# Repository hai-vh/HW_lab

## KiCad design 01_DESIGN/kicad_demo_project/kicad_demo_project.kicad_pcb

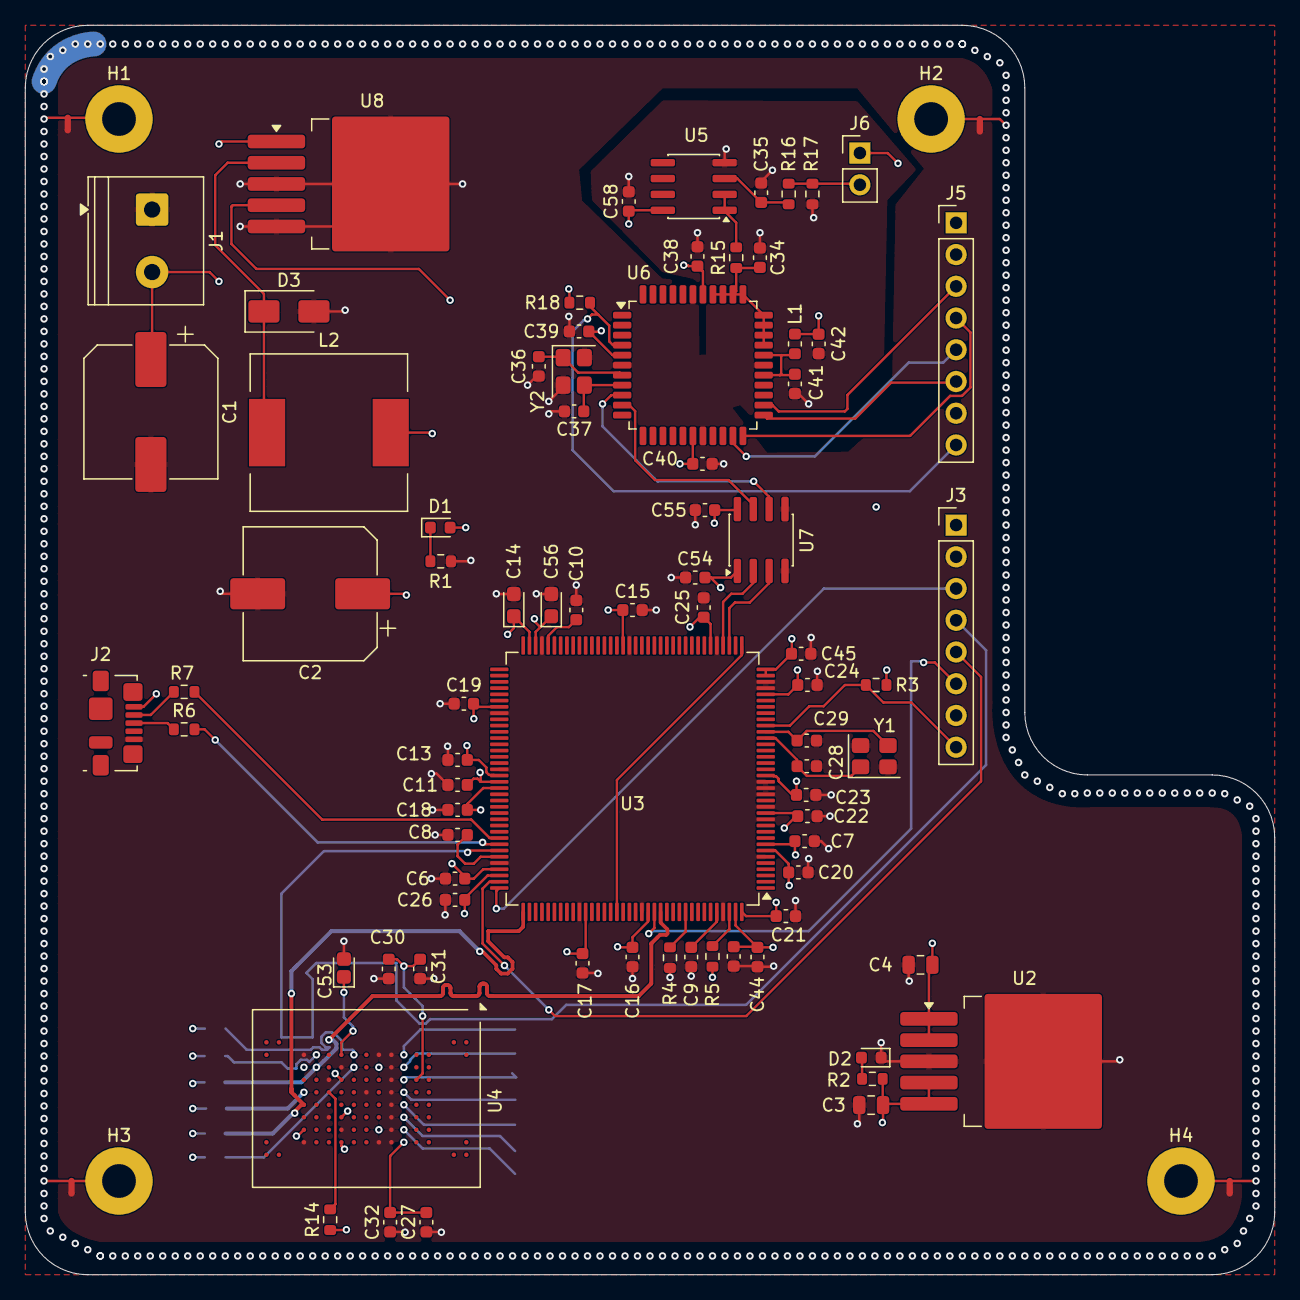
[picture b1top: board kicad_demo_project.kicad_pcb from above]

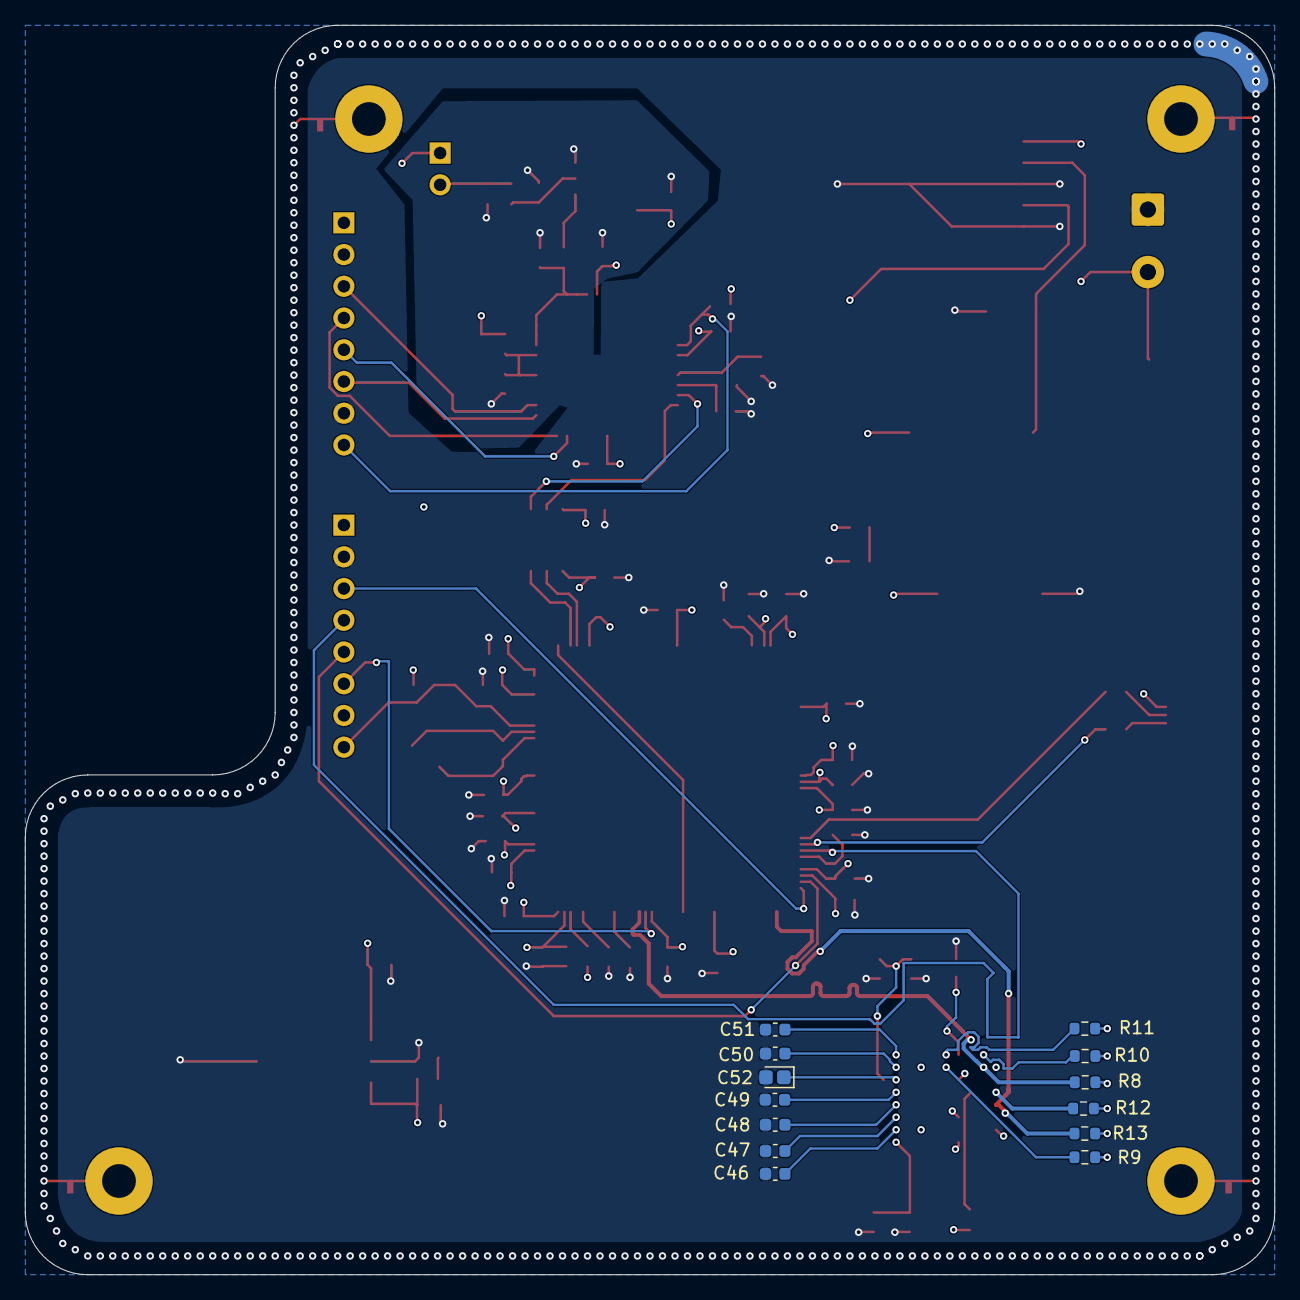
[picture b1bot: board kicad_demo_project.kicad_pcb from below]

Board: 4 copper layers, 100.0 x 100.0 mm, 99 parts (13 on the bottom side), 49 nets.

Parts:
C1: 680uF; CP_Elec_10x10.5
C2: 220uF; CP_Elec_10x10.5
C3, C4: 10uF; C_0805_2012Metric
C6, C7, C11, C15, C16, C17, C18, C19, C20, C21, C22, C23, C24, C25, C26, C27, C30, C32, C34, C35, C38, C39, C40, C41, C42, C44, C45, C46, C47, C48, C49, C50, C51, C54, C55, C58: 0.1uF/6.3V; C_0603_1608Metric
C8, C9, C10, C13: 4.7uF/6.3V; C_0603_1608Metric
C14, C56: 4.7uF; CP_EIA-2012-15_AVX-P
C28, C29, C36, C37: 16pF/6.3V; C_0603_1608Metric
C31: 1uF/6.3V; C_0603_1608Metric
C43: 0.1uF/6.3V; CAP_C_1608X80
C52, C53: 4.7uF; CP_EIA-1608-10_AVX-L
D1, D2: 150060YS75000; LED_0603_1608Metric
D3: SS34; D_SMA
H1, H2, H3, H4: MountingHole_Pad; MountingHole_2.7mm_M2.5_Pad
J1: Screw_Terminal_01x02; TerminalBlock_Phoenix_PT-1,5-2-5.0-H_1x02_P5.00mm_Horizontal
J2: 0473460001; USB_Micro-B_Molex_47346-0001
J3, J5: Conn_01x08; PinHeader_1x08_P2.54mm_Vertical
J6: Conn_01x02; PinHeader_1x02_P2.54mm_Vertical
L1: 10uH/250mA; L_0603_1608Metric
L2: 47uH; L_12x12mm_H8mm
NT1, NT2, NT3, NT4: NetTie_2; NetTie-2_SMD_Pad0.5mm
R1, R2: 1k; R_0603_1608Metric
R3, R4, R5, R14, R18: 4.7k; R_0603_1608Metric
R6, R7: 0R/DNP; R_0603_1608Metric
R8, R9, R10, R11, R12, R13, R17: 10k; R_0603_1608Metric
R15, R16: 22R; R_0603_1608Metric
U2: TPS7A4533DCQR; TO-263-5_TabPin3
U3: STM32H745ZIT3; LQFP-144_20x20mm_P0.5mm
U4: MTFC32GAZAQDW-AAT; BGA-100_14x18mm_Layout10x17_P1mm
U5: OPA2340; SOIC-8_3.9x4.9mm_P1.27mm
U6: ATMEGA324PA; TQFP-44_10x10mm_P0.8mm
U7: ISO7721DR; SOIC-8_3.9x4.9mm_P1.27mm
U8: LM2596S-5; TO-263-5_TabPin3
Y1, Y2: Crystal_GND24; Crystal_SMD_3225-4Pin_3.2x2.5mm

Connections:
+3.3V: C3.1, C6.2, C7.2, C11.2, C13.2, C14.1, C15.2, C16.2, C17.2, C18.2, C19.2, C20.2, C21.2, C22.2, C23.2, C24.2, C25.2, C26.2, C27.2, C32.2, C43.2, C44.2, C45.2, C46.2, C47.2, C48.2, C49.2, C50.2, C51.2, C52.1, C53.1, C54.2, C56.1, J3.1, R2.2, R3.1, R5.1, R8.2, R9.2, R10.2, R11.2, R12.2, R13.2, R14.1, U2.4 (OUT), U2.5 (SENSE), U3.7 (VDD), U3.8 (VBAT), U3.13 (VDD), U3.19 (VDD), U3.32 (VDD), U3.35 (VREF+), U3.36 (VDDA), U3.42 (VDD), U3.56 (VDD), U3.70 (VDDLDO), U3.71 (VDD), U3.79 (VDD), U3.90 (VDD50USB), U3.91 (VDD33USB), U3.92 (VDD), U3.105 (VDDLDO), U3.106 (VDD), U3.119 (VDD), U3.129 (VDD), U3.143 (VDDLDO), U3.144 (VDD), U4.F2 (VCC), U4.F3 (VCC), U4.F4 (VCC), U4.F5 (VCC), U4.F6 (VCC), U4.F7 (VCC), U4.F8 (VCC), U4.F9 (VCC), U4.H3 (VCCQ), U4.H8 (VCCQ), U4.L2 (VCCQ), U4.L4 (VCCQ), U4.L7 (VCCQ), U4.L9 (VCCQ), U4.P3 (VCCQ), U4.P8 (VCCQ), U7.1 (VCC1)
+5V: C2.1, C4.1, C38.2, C39.2, C40.2, C42.2, C55.2, C58.1, D1.2 (A), J2.1 (VBUS), J5.1, J6.1, L1.2, L2.2, R18.2, U2.1 (~SHDN), U2.2 (IN), U5.8 (V+), U6.5 (VCC), U6.17 (VCC), U6.38 (VCC), U7.8 (VCC2), U8.4 (FB)
+5V_AVCC: C41.2, L1.1, U6.27 (AVCC), U6.29 (AREF)
+12V: C1.1, J1.2, U8.1 (VIN)
/AVR/ADC_TEMP1: C34.2, R15.1, U6.30 (PA7_(ADC7/PCINT7)), U6.31 (PA6_(ADC6/PCINT6)), U6.32 (PA5_(ADC5/PCINT5)), U6.33 (PA4_(ADC4/PCINT4)), U6.34 (PA3_(ADC3/PCINT3)), U6.35 (PA2_(ADC2/PCINT2)), U6.36 (PA1_(ADC1/PCINT1)), U6.37 (PA0_(ADC0/PCINT0))
/AVR/AVR_JTAG_TCK: J5.5, U6.21 (PC2_(PCINT18/TCK))
/AVR/AVR_JTAG_TDI: J5.3, U6.24 (PC5_(TDI/PCINT21))
/AVR/AVR_JTAG_TDO: J5.6, U6.23 (PC4_(TDO/PCINT20))
/AVR/AVR_JTAG_TMS: J5.4, U6.22 (PC3_(PCINT19/TMS))
/AVR/AVR_JTAG_nRESET: J5.8, R18.1, U6.4 (~RESET)
/AVR/NTC1-: J6.2, R16.2, R17.1
/MCU/MCU_BOOT0: R4.2, U3.135 (BOOT0)
/MCU/MCU_JTAG_TCK: J3.5, U3.107 (PA14)
/MCU/MCU_JTAG_TDI: J3.3, U3.108 (PA15)
/MCU/MCU_JTAG_TDO: J3.6, U3.130 (PB3)
/MCU/MCU_JTAG_TMS: J3.4, U3.102 (PA13)
/MCU/MCU_JTAG_nRESET: J3.8, R3.2, U3.27 (~RST)
/MCU/MCU_OSCIN: C28.1, U3.25 (PH0-OSC_IN), Y1.1
/MCU/MCU_OSCOUT: C29.1, U3.26 (PH1-OSC_OUT), Y1.3
/MCU/MCU_PDR: R5.2, U3.142 (PDR_ON)
/MCU/MCU_VCAP1: C10.2, U3.68 (VCAP)
/MCU/MCU_VCAP2: C8.2, U3.103 (VCAP)
/MCU/MCU_VCAP3: C9.2, U3.140 (VCAP)
/MCU/MCU_eMMC_SDMMC2_D2: U3.37 (PA0), U3.124 (PG11)
/MCU/USB_2.0_CONN_N: J2.2 (D-), R7.1
/MCU/USB_2.0_CONN_P: J2.3 (D+), R6.1
/MCU/USB_2.0_D_N: R7.2, U3.100 (PA11)
/MCU/USB_2.0_D_P: R6.2, U3.101 (PA12)
/POWER/SHIELDING: H1.1 (1_1), H2.1 (1_1), H3.1 (1_1), H4.1 (1_1), NT1.2, NT2.2, NT3.2, NT4.2
/eMMC/EMMC2_nRST: R14.2, U4.M5 (RST_n)
/eMMC/MCU_eMMC_SDMMC2_D0: R11.1, U4.K2 (DAT0)
/eMMC/MCU_eMMC_SDMMC2_D1: R10.1, U4.N2 (DAT1)
/eMMC/MCU_eMMC_SDMMC2_D2: R9.1, U4.K3 (DAT2)
AVR_ISO_UART0_RX: U6.9 (PD0_(PCINT24/RXD0/T3)), U7.6 (OUTB)
AVR_ISO_UART0_TX: U6.10 (PD1_(PCINT25/TXD0)), U7.7 (INA)
GND: C1.2, C2.2, C3.2, C4.2, C6.1, C7.1, C8.1, C9.1, C10.1, C11.1, C13.1, C14.2, C15.1, C16.1, C17.1, C18.1, C19.1, C20.1, C21.1, C22.1, C23.1, C24.1, C25.1, C26.1, C27.1, C28.2, C29.2, C30.1, C31.1, C32.1, C34.1, C35.1, C36.2, C37.2, C38.1, C39.1, C40.1, C41.1, C42.1, C43.1, C44.1, C45.1, C46.1, C47.1, C48.1, C49.1, C50.1, C51.1, C52.2, C53.2, C54.1, C55.1, C56.2, C58.2, D2.1 (K), D3.2 (A), J1.1, J2.5 (GND), J3.2, J3.7, J5.2, J5.7, NT1.1, NT2.1, NT3.1, NT4.1, R1.2, R4.1, R17.2, U2.3 (GND), U3.6 (VSS), U3.12 (VSS), U3.14 (VSSSMPS), U3.16 (VDDSMPS), U3.17 (VFBSMPS), U3.18 (VSS), U3.33 (VSS), U3.34 (VSSA), U3.41 (VSS), U3.55 (VSS), U3.69 (VSS), U3.80 (VSS), U3.89 (VSS), U3.104 (VSS), U3.118 (VSS), U3.128 (VSS), U3.141 (VSS), U4.G2 (VSS), U4.G3 (VSS), U4.G4 (VSS), U4.G5 (VSS), U4.G6 (VSS), U4.G7 (VSS), U4.G8 (VSS), U4.G9 (VSS), U4.H2 (VSSQ), U4.H9 (VSSQ), U4.J5 (VSS), U4.L3 (VSSQ), U4.L8 (VSSQ), U4.M4 (VSSQ), U4.M7 (VSSQ), U4.P2 (VSSQ), U4.P9 (VSSQ), U5.4 (V-), U6.6 (GND), U6.18 (GND), U6.28 (GND), U6.39 (GND), U7.4 (GND1), U7.5 (GND2), U8.3 (GND), U8.5 (~ON/OFF), Y1.2 (G), Y1.4 (G), Y2.2 (G), Y2.4 (G)
MCU_ISO_UART2_RX: U3.40 (PA3), U7.2 (OUTA)
MCU_ISO_UART2_TX: U3.39 (PA2), U7.3 (INB)
MCU_eMMC_SDMMC2_CK: R13.1, U3.109 (PC10), U4.P6 (CLK)
MCU_eMMC_SDMMC2_CMD: R12.1, U4.P5 (CMD)
MCU_eMMC_SDMMC2_D3: R8.1, U3.131 (PB4), U4.N3 (DAT3)
unnamed: D1.1 (K), R1.1
unnamed: D2.2 (A), R2.1
unnamed: D3.1 (K), L2.1, U8.2 (OUT)
unnamed: C30.2, C31.2, U4.E4 (VDDIM)
unnamed: C35.2, R16.1, U5.3 (+)
unnamed: R15.2, U5.1, U5.2 (-)
unnamed: C37.1, U6.8 (XTAL1), Y2.3
unnamed: C36.1, U6.7 (XTAL2), Y2.1

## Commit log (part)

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2026-06-22 Add gitkeep files
2026-06-28 Update schematic, PCB
